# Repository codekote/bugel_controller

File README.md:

# bugel_controller based on 555 timers (KiCad)

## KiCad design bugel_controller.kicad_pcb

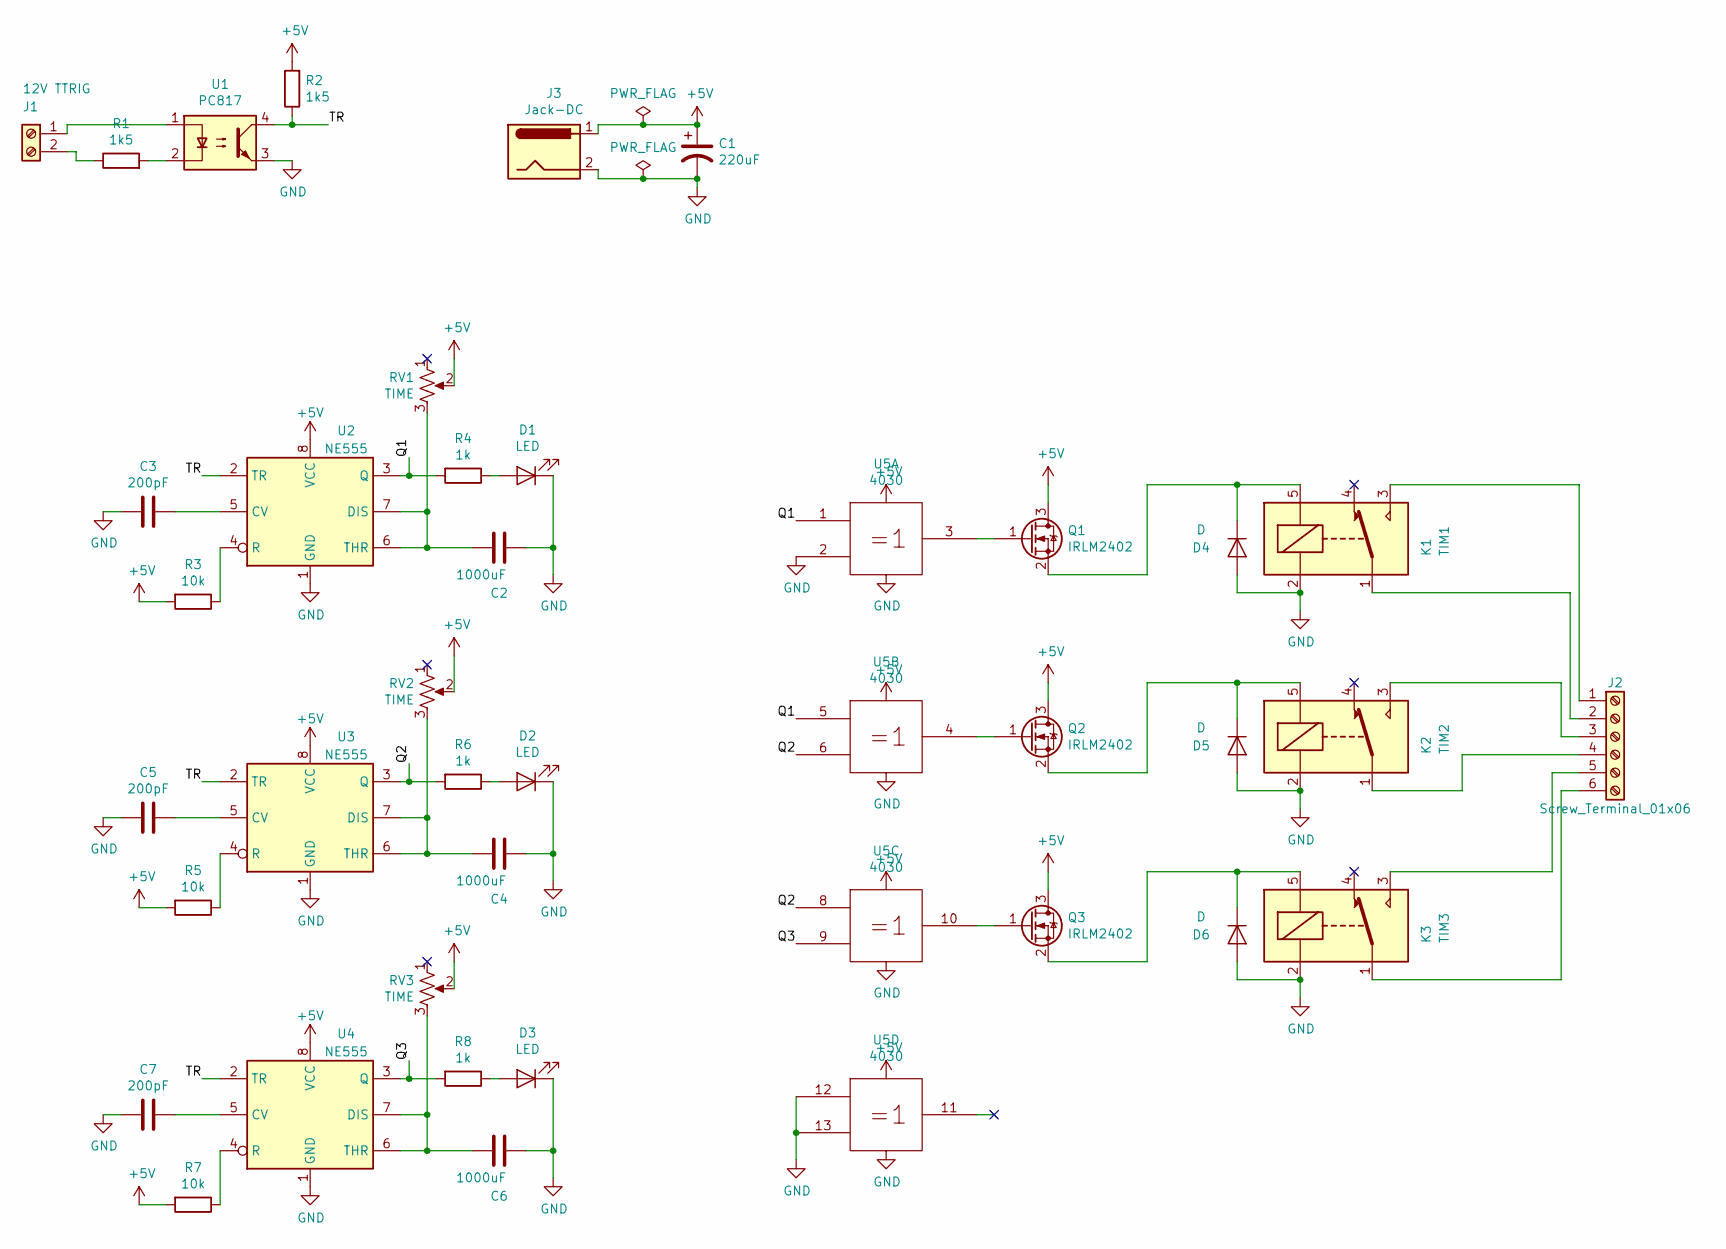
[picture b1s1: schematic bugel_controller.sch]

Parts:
C1: 220uF; CP_Radial_D6.3mm_P2.50mm
C2, C4, C6: 1000uF; CP_Radial_D8.0mm_P2.50mm
C3, C5, C7: 200pF; C_Disc_D6.0mm_W4.4mm_P5.00mm
D1, D2, D3: LED; LED_1206_3216Metric
D4, D5, D6: D; D_DO-15_P10.16mm_Horizontal
J1: 12V TTRIG; TerminalBlock_bornier-2_P5.08mm
J2: Screw_Terminal_01x06; TerminalBlock_bornier-6_P5.08mm
J3: Jack-DC; BarrelJack_Horizontal
K1: TIM1; Relay_SPDT_SANYOU_SRD_Series_Form_C
K2: TIM2; Relay_SPDT_SANYOU_SRD_Series_Form_C
K3: TIM3; Relay_SPDT_SANYOU_SRD_Series_Form_C
Q1, Q2, Q3: IRLM2402; SOT-23
R1, R2: 1k5; R_Axial_DIN0207_L6.3mm_D2.5mm_P10.16mm_Horizontal
R3, R5, R7: 10k; R_Axial_DIN0207_L6.3mm_D2.5mm_P10.16mm_Horizontal
R4, R6, R8: 1k; R_Axial_DIN0207_L6.3mm_D2.5mm_P10.16mm_Horizontal
RV1, RV2, RV3: TIME; Potentiometer_Bourns_3266W_Vertical
U1: PC817; DIP-4_W7.62mm
U2, U3, U4: NE555; SMDIP-8_W7.62mm
U5: 4030; DIP-14_W7.62mm_LongPads

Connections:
+5V: C1.1, J3.1, Q1.3 (D), Q2.3 (D), Q3.3 (D), R2.2, R3.2, R5.2, R7.2, RV1.2, RV2.2, RV3.2, U2.8 (VCC), U3.8 (VCC), U4.8 (VCC), U5.14 (Vdd)
/Q1: R4.2, U2.3 (Q), U5.1, U5.5
/Q2: R6.2, U3.3 (Q), U5.6, U5.8
/Q3: R8.2, U4.3 (Q), U5.9
/TR: R2.1, U1.4, U2.2 (TR), U3.2 (TR), U4.2 (TR)
GND: C1.2, C2.2, C3.2, C4.2, C5.2, C6.2, C7.2, D1.1 (K), D2.1 (K), D3.1 (K), D4.2 (A), D5.2 (A), D6.2 (A), J3.2, K1.2, K2.2, K3.2, U1.3, U2.1 (GND), U3.1 (GND), U4.1 (GND), U5.2, U5.7 (Vss), U5.12, U5.13
unnamed: C2.1, RV1.3, U2.6 (THR), U2.7 (DIS)
unnamed: C3.1, U2.5 (CV)
unnamed: C4.1, RV2.3, U3.6 (THR), U3.7 (DIS)
unnamed: C5.1, U3.5 (CV)
unnamed: C6.1, RV3.3, U4.6 (THR), U4.7 (DIS)
unnamed: C7.1, U4.5 (CV)
unnamed: D1.2 (A), R4.1
unnamed: D2.2 (A), R6.1
unnamed: D3.2 (A), R8.1
unnamed: D4.1 (K), K1.5, Q1.2 (S)
unnamed: D5.1 (K), K2.5, Q2.2 (S)
unnamed: D6.1 (K), K3.5, Q3.2 (S)
unnamed: J1.1, U1.1
unnamed: J1.2, R1.1
unnamed: J2.1, K1.3
unnamed: J2.2, K1.1
unnamed: J2.3, K2.3
unnamed: J2.4, K2.1
unnamed: J2.5, K3.3
unnamed: J2.6, K3.1
unnamed: Q1.1 (G), U5.3
unnamed: Q2.1 (G), U5.4
unnamed: Q3.1 (G), U5.10
unnamed: R1.2, U1.2
unnamed: R3.1, U2.4 (R)
unnamed: R5.1, U3.4 (R)
unnamed: R7.1, U4.4 (R)

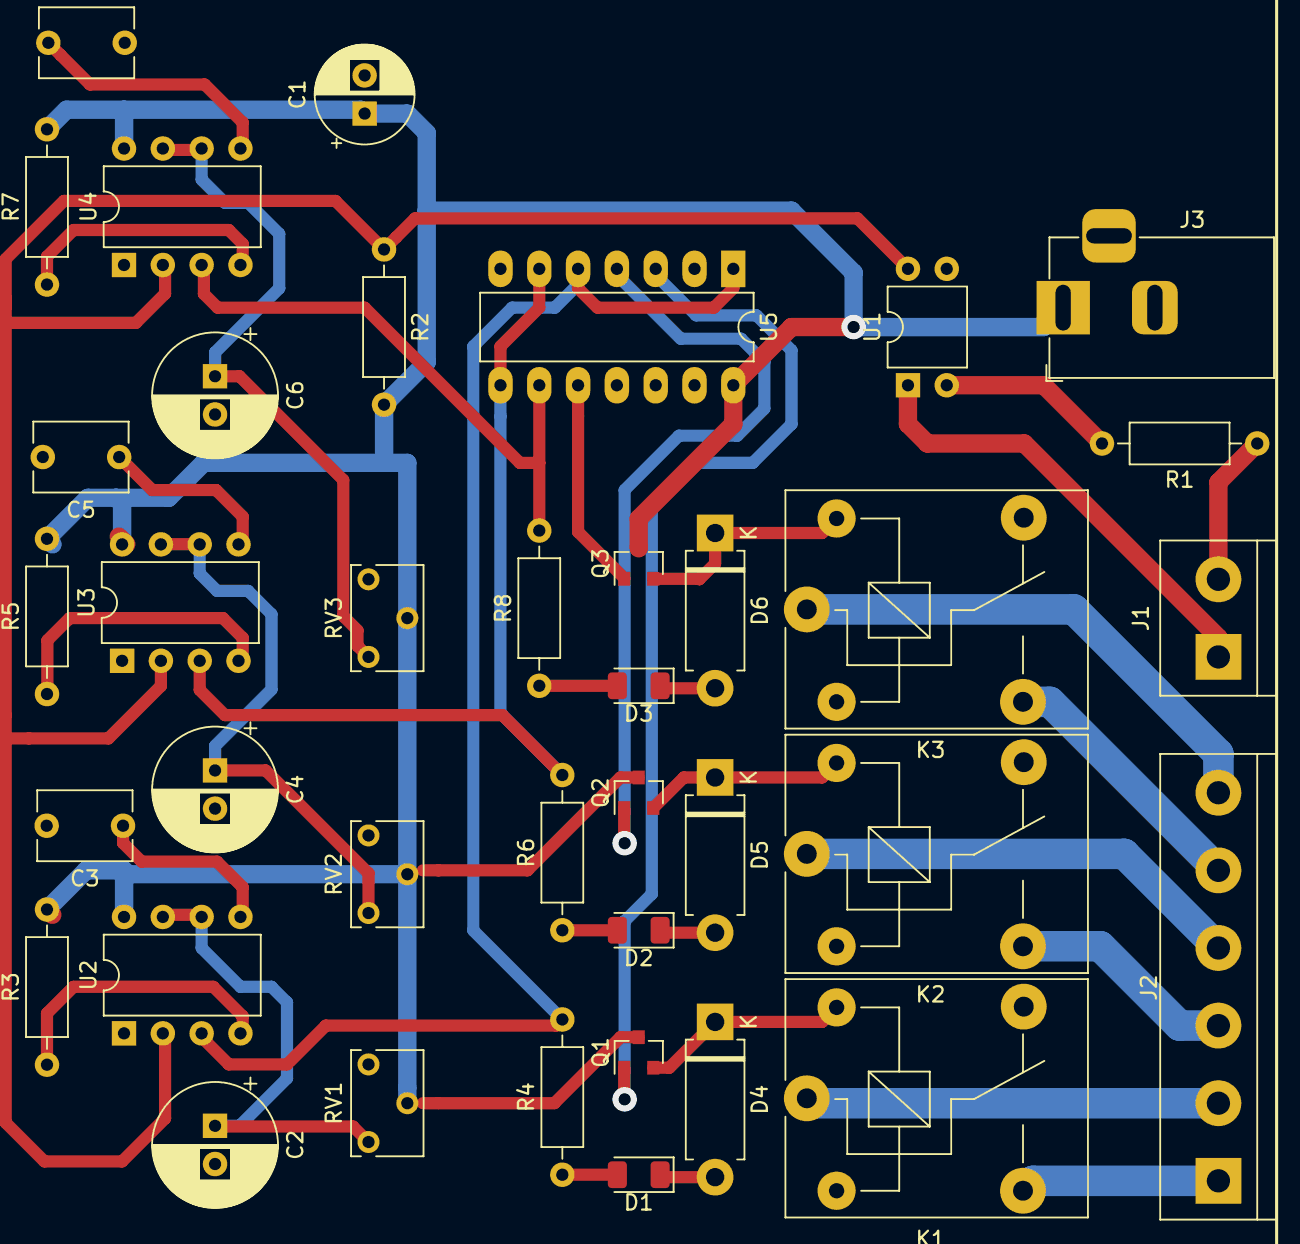
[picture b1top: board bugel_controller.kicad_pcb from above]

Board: 2 copper layers, 38 parts (0 on the bottom side), 33 nets.

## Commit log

2020-08-03 add 3d-view-pcb
